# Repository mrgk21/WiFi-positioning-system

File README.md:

# WiFi-positioning-system

It trilaterates the position of the broker using RSSI values from all the nodes
Based on MQTT protocol and using the log model for calculation distances from RSSI values
Uses kalman filter for filtering out erratic data in real-time (Assumption: External noises are null)
You are to run all the python scripts concurrently

Software:
1. MongoDB
2. Mosquitto Broker

Hardware:
1. NodeMCU as nodes
2. Raspi as server/broker

Modes for failure:
1. Change the AP ssid and pass in the code from all the nodes
2. The mongoDB and mosquitto broker are left open in the project, add pass in code if needed.
3. Keep the server in a relatively open open space to reduce multipath fading
4. Change the RSSI @ 1m in the node.py codes
5. Change (x, y) coordinates of al the nodes in trilateration.py
6. Calculate the loss factor

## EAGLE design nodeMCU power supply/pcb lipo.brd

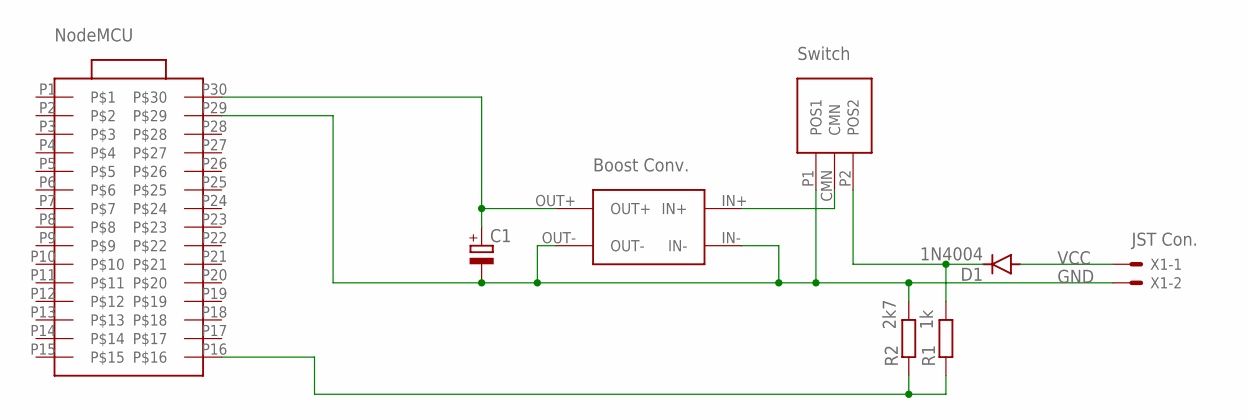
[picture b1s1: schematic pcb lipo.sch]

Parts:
C1: CPOL-EUE1.8-4; E1,8-4
D1: 1N4004; DO41-10
R1: 1k; 0207/7
R2: 2k7; 0207/7
U$1: NODEMCU; DIP
U$2: MODULE
U$3: SWITCH; DIP
X1: 22-23-2021

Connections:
GND: C1.-, R2.2, U$1.P29, U$2.IN-, U$2.OUT-, U$3.P1 (POS1), X1.2
unnamed: C1.+, U$1.P30, U$2.OUT+
unnamed: U$2.IN+, U$3.CMN
unnamed: D1.C, R1.2, U$3.P2 (POS2)
unnamed: R1.1, R2.1, U$1.P16
VCC: D1.A, X1.1

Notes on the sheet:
NodeMCU
Boost Conv.
Switch
JST Con.

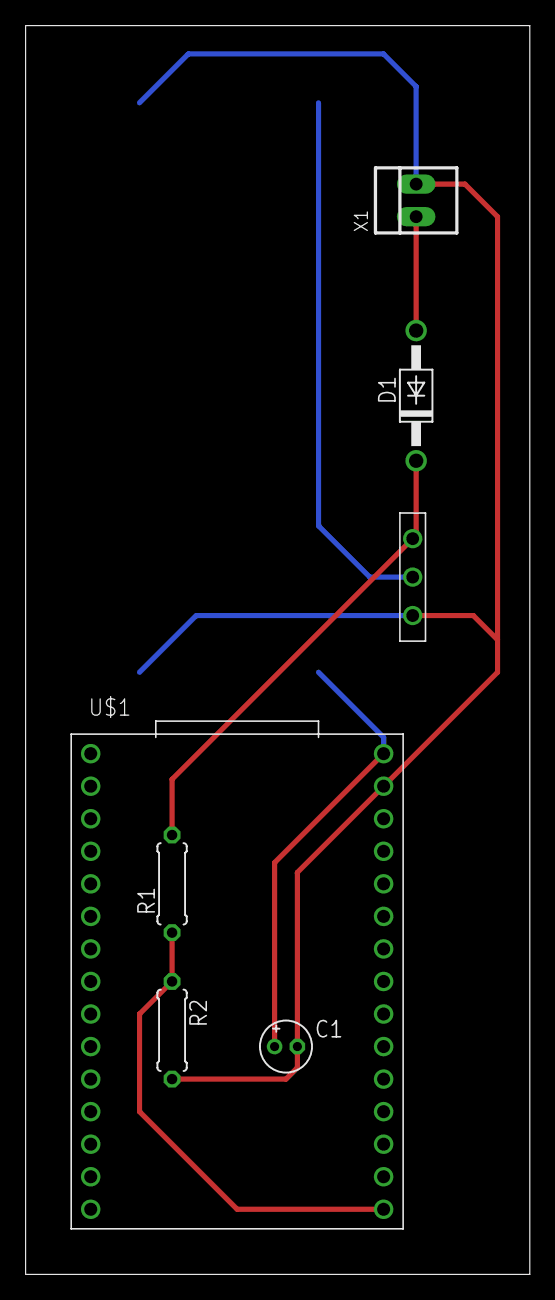
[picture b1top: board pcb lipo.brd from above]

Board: 2 copper layers, 39.3 x 97.5 mm, 8 parts (1 on the bottom side), 6 nets.
